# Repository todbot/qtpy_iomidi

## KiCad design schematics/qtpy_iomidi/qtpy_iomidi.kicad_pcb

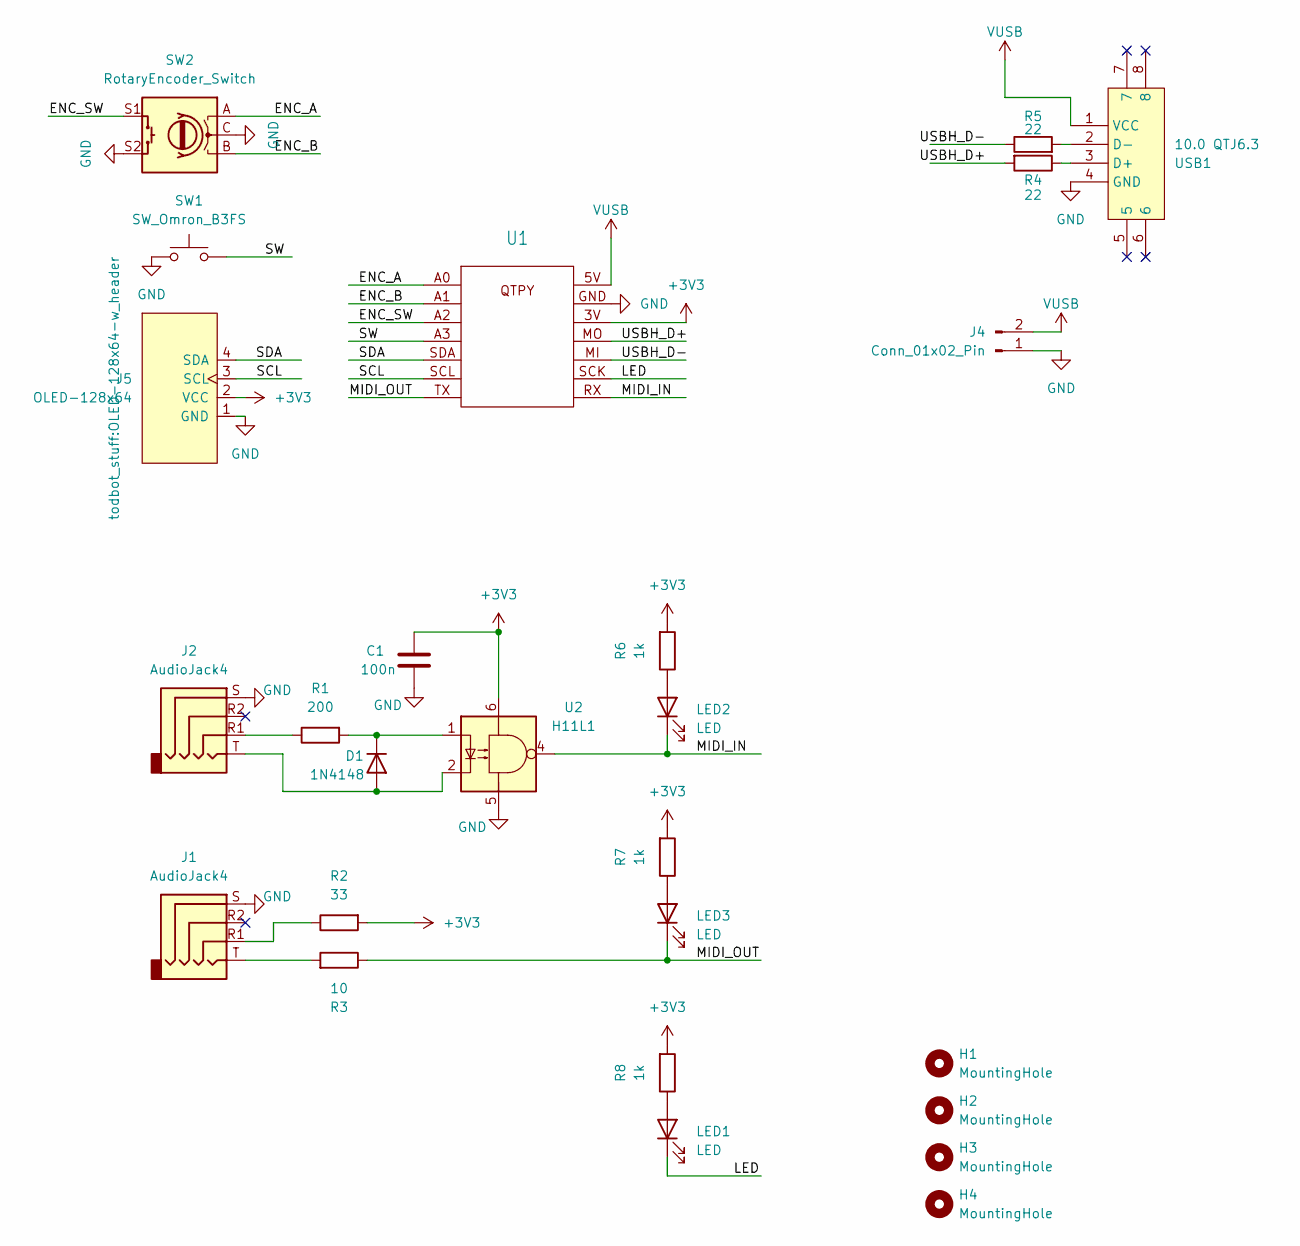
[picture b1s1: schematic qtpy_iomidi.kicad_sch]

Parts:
C1: 100n; C_0805_2012Metric
D1: 1N4148; D_SOD-123
H1, H2, H3, H4: MountingHole; MountingHole_2.7mm_M2.5
J1, J2: AudioJack4; Jack_3.5mm_PJ320D_Horizontal; LCSC C431535
J4: Conn_01x02_Pin; PinHeader_1x02_P2.54mm_Vertical
J5: OLED-128x64; OLED-128x64-w_header
LED1, LED2, LED3: LED; LED_0805_2012Metric; LCSC C49678
R1: 200; R_0805_2012Metric
R2: 33; R_0805_2012Metric
R3: 10; R_0805_2012Metric
R4, R5: 22; R_0805_2012Metric
R6, R7, R8: 1k; R_0805_2012Metric
SW1: SW_Omron_B3FS; SW_PUSH_6mm_H4.3mm
SW2: RotaryEncoder_Switch; RotaryEncoder_Alps_EC11E-Switch_Vertical_H20mm_CircularMoun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
U1: QTPY_TH_HEADERSOCKET
U2: H11L1; DIP-6_W8.89mm_SMDSocket_LongPads; LCSC C78589
USB1: 10.0 QTJ6.3; USB-A-SMD_10.0-QTJ6.3; LCSC Part C404966

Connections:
+3V3: C1.1, J5.2 (VCC), R2.2, R6.2, R7.2, R8.2, U1.3V, U2.6
/ENC_A: SW2.A, U1.A0
/ENC_B: SW2.B, U1.A1 (9)
/ENC_SW: SW2.S1, U1.A2
/LED: LED1.1 (K), U1.SCK
/MIDI_IN: LED2.1 (K), U1.RX, U2.4
/MIDI_OUT: LED3.1 (K), R3.1, U1.TX
/SCL: J5.3 (SCL), U1.SCL
/SDA: J5.4 (SDA), U1.SDA
/SW: SW1.2, U1.A3
/USBH_D+: R4.2, U1.MO
/USBH_D-: R5.1, U1.MI
GND: C1.2, J1.S, J2.S, J4.1, J5.1 (GND), SW1.1, SW2.C, SW2.S2, U1.GND (14), U2.5, USB1.4 (GND)
unnamed: D1.2 (A), J2.T, U2.2
unnamed: D1.1 (K), R1.2, U2.1
unnamed: J1.R1, R2.1
unnamed: J1.T, R3.2
unnamed: J2.R1, R1.1
unnamed: LED1.2 (A), R8.1
unnamed: LED2.2 (A), R6.1
unnamed: LED3.2 (A), R7.1
unnamed: R4.1, USB1.3 (D+)
unnamed: R5.2, USB1.2 (D-)
VUSB: J4.2, U1.5V, USB1.1 (VCC)

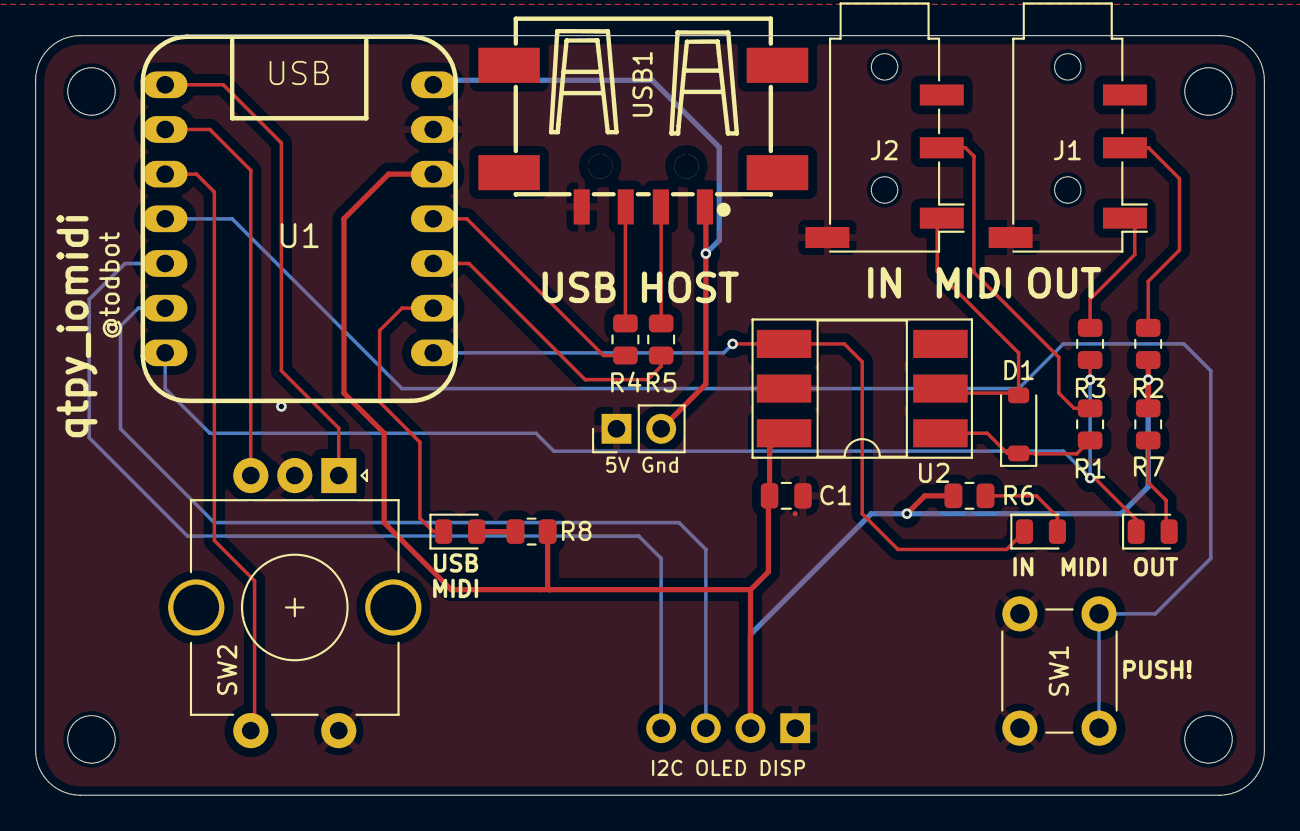
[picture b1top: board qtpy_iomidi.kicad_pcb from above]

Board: 2 copper layers, 69.8 x 43.2 mm, 26 parts (0 on the bottom side), 24 nets.

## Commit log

2024-05-11 first
2024-05-11 some silkscreen
2024-05-13 switch to LCSC USB SMD host jack, add display & switch
2024-05-13 pcb tweaks
2024-05-14 more pcb tweaking
2024-05-17 added encoder
2024-05-18 submit to fab
2024-06-10 qtpy holes too small, fixed I think
